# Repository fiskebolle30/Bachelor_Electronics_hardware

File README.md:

# Bachelor_Electronics_hardware
All PCB design files for the bachelor project. Project is made in KiCad

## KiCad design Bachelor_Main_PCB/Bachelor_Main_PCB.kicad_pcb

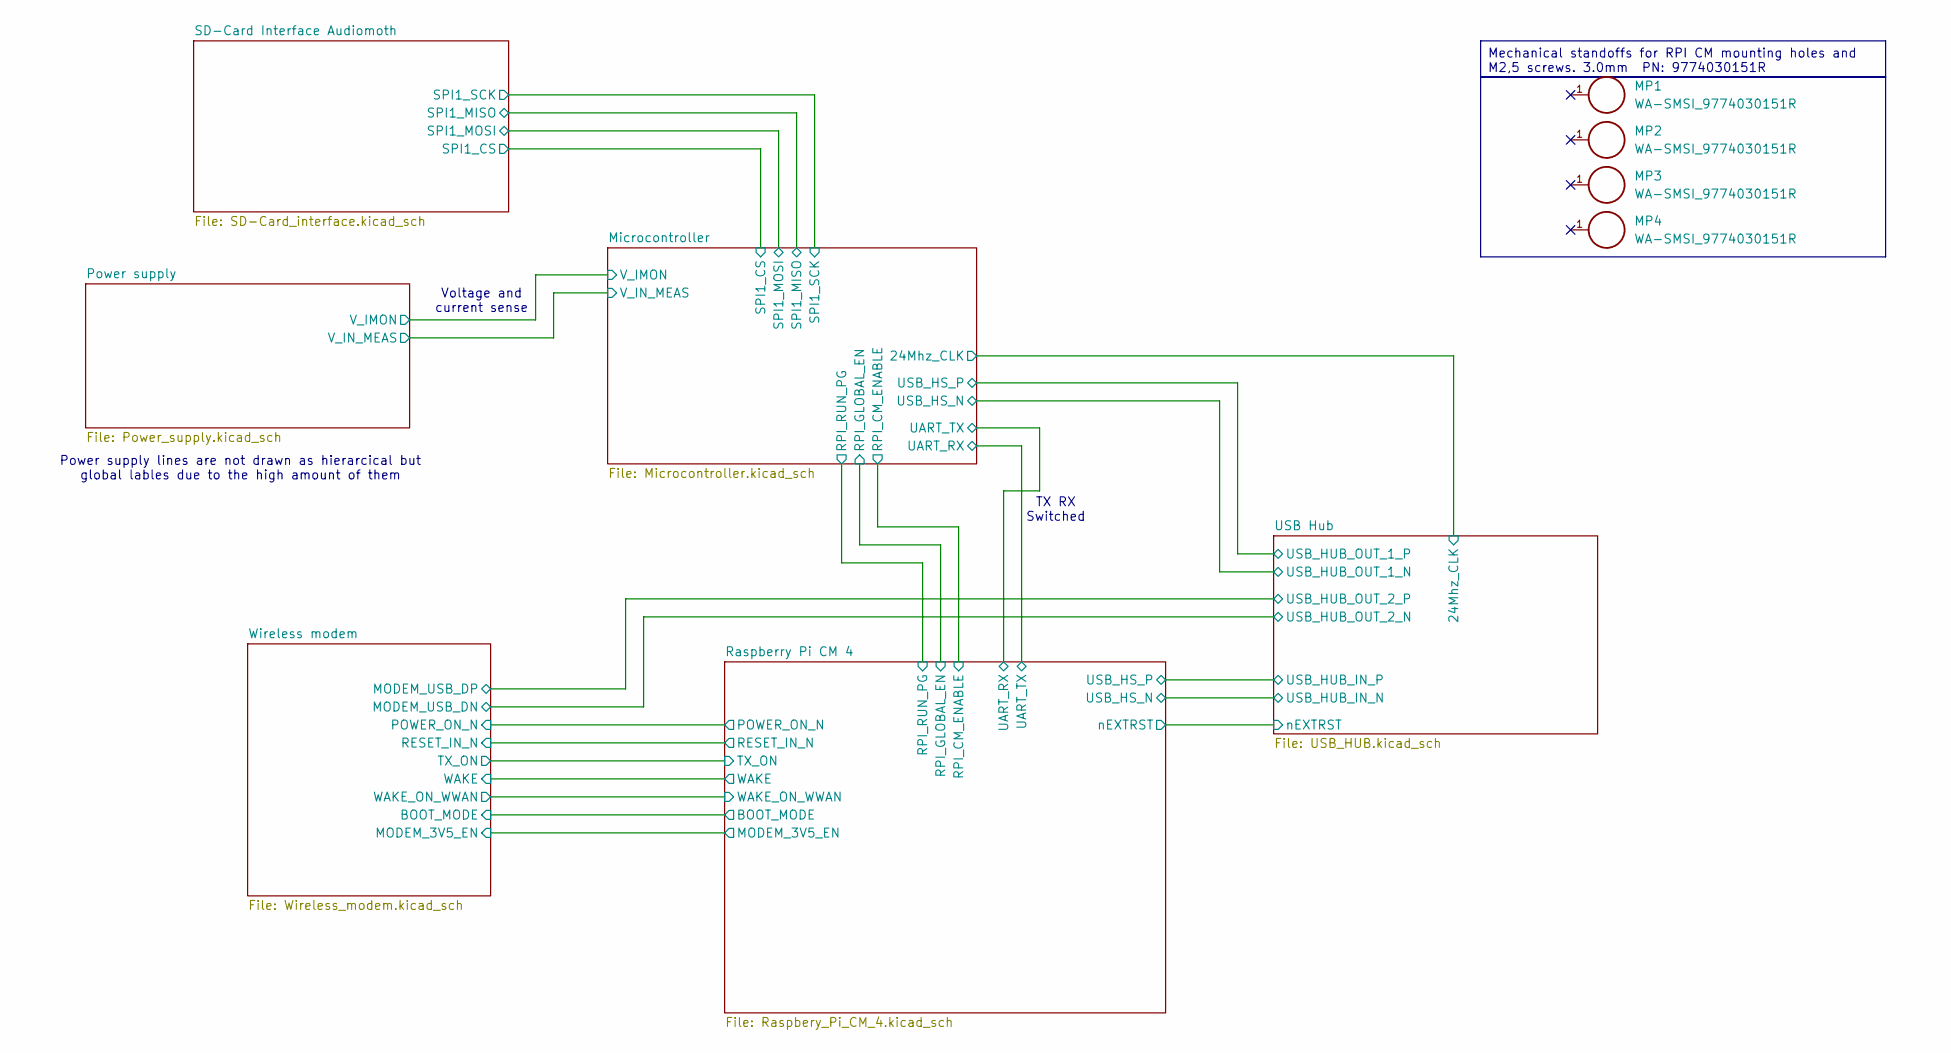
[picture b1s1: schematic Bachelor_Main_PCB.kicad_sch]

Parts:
MP1, MP2, MP3, MP4: WA-SMSI_9774030151R; WA-SMSI_9774030151; PART-NUMBER 9774030151R

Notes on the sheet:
TX RX Switched
Voltage and current sense
Power supply lines are not drawn as hierarcical but global lables due to the high amount of them
Mechanical standoffs for RPI CM mounting holes and M2,5 screws. 3.0mm PN: 9774030151R

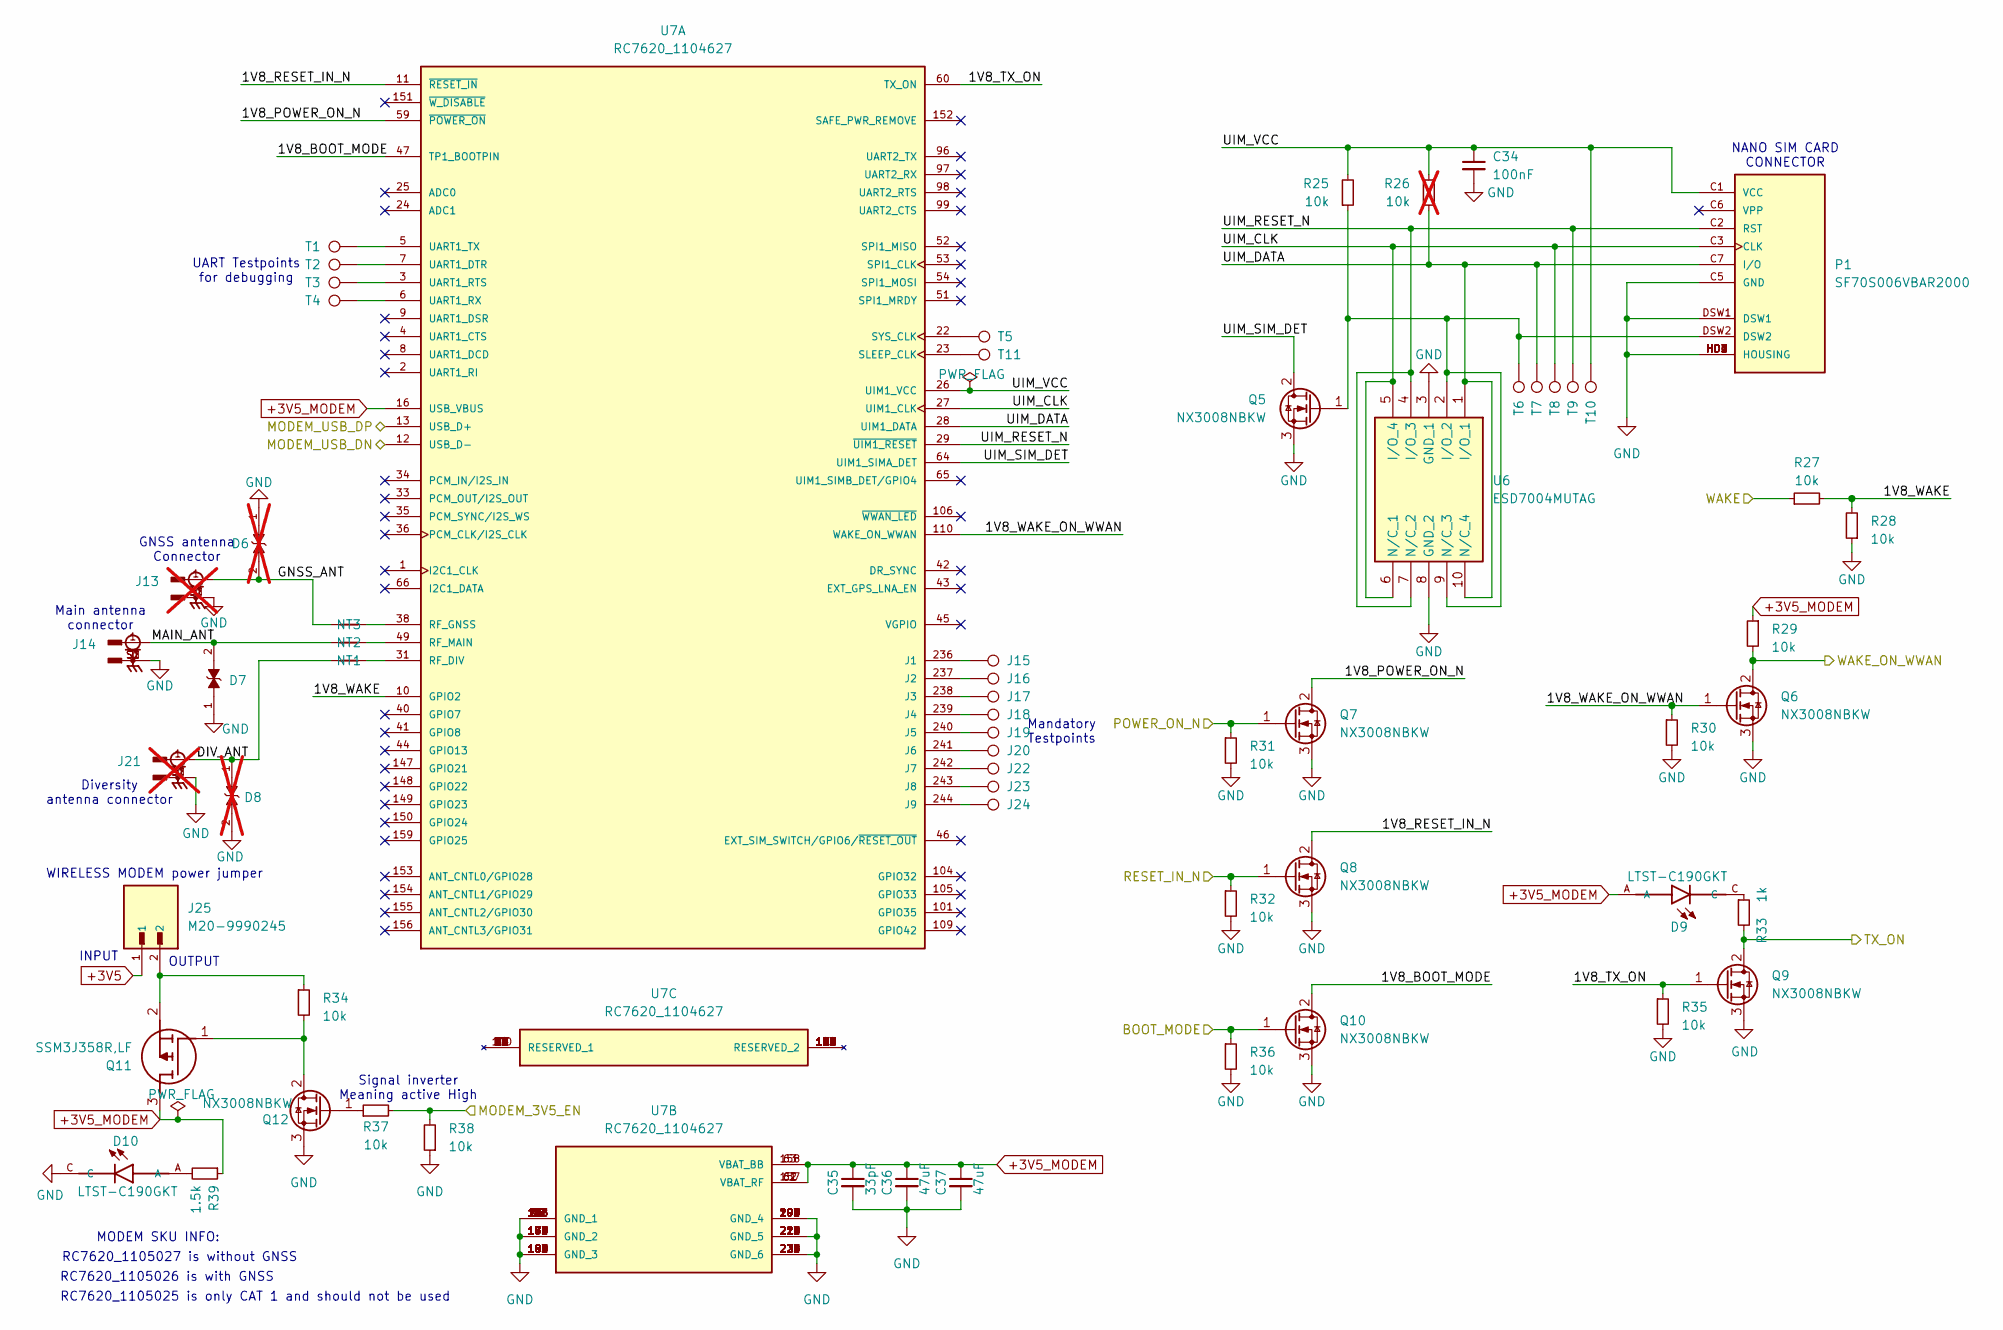
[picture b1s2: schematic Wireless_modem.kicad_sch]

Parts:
C34: 100nF; C_0603_1608Metric; Voltage 50V; Voltage rating 50v; MPN GRM155R71H104KE14D; Mouser 81-GRM155R71H104KE4D
C35: 33pF; C_0603_1608Metric; Voltage rating 50v; Part-no CL10C330JB8NNNC
C36, C37: 47uF; C_1206_3216Metric; Voltage rating 10v; Part-no GRM31CR61A476ME15L
D6, D8: 0402ESDA-MLP1; ESD_0402ESDA-MLP1; Part-no 0402ESDA-MLP1; not fitted
D7: 0402ESDA-MLP1; ESD_0402ESDA-MLP1; Part-no 0402ESDA-MLP1
D9, D10: LTST-C190GKT; LEDM1608X80; Part-no LTST-C190GKT
J13, J21: CONMHF1-SMD-G-T; LINX_CONMHF1-SMD-G-T; Part-no CONMHF1-SMD-G-T; not fitted
J14: CONMHF1-SMD-G-T; LINX_CONMHF1-SMD-G-T; Part-no CONMHF1-SMD-G-T
J15, J16, J17, J18, J19, J20, J22, J23, J24: TestPoint_Pad_D1.0mm
J25: M20-9990245; HARWIN_M20-9990245; PARTREV 14
NT1, NT2, NT3: NetTie_2; 0.3mm_to_0.41_net_tie
P1: SF70S006VBAR2000; JAE_SF70S006VBAR2000
Q5, Q6, Q7, Q8, Q9, Q10, Q12: NX3008NBKW; SOT-323_SC-70; MPN NX3008NBKW; Digikey 1727-1280-6-ND
Q11: SSM3J358R,LF; SOTFL95P240X88-3N; Manufacturer_Part_Number SSM3J358R,LF; Mouser Part Number 757-SSM3J358RLF
R25, R27, R28, R29, R30, R31, R32, R34, R35, R36, R37, R38: 10k; R_0603_1608Metric; Part-no RC0603FR-0710KL
R26: 10k; R_0603_1608Metric; not fitted
R33: 1k; R_0603_1608Metric
R39: 1.5k; R_0603_1608Metric
T1, T2, T3, T4, T5, T6, T7, T8, T9, T10, T11: TestPoint_Pad_D1.0mm
U6: ESD7004MUTAG; UDFN10_CASE_517BB; Manufacturer_Part_Number ESD7004MUTAG; Mouser Part Number 863-ESD7004MUTAG
U7: RC7620_1104627; XCVR_RC7620_1104625; PARTREV 12

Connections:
+3V5: J25.1; also elsewhere on the board
+3V5_MODEM: C35.1, C36.1, C37.1, D9.A, Q11.3 (D), R29.1, R39.1, U7.16 (USB_VBUS), U7.61 (VBAT_RF), U7.62 (VBAT_RF), U7.63 (VBAT_BB), U7.157 (VBAT_RF), U7.158 (VBAT_BB)
/Raspberry Pi CM 4/BOOT_MODE: Q10.1 (G), R36.1; also elsewhere on the board
/Raspberry Pi CM 4/MODEM_3V5_EN: R37.2, R38.2; also elsewhere on the board
/Raspberry Pi CM 4/POWER_ON_N: Q7.1 (G), R31.1; also elsewhere on the board
/Raspberry Pi CM 4/RESET_IN_N: Q8.1 (G), R32.1; also elsewhere on the board
/Raspberry Pi CM 4/TX_ON: Q9.2 (D), R33.2; also elsewhere on the board
/Raspberry Pi CM 4/WAKE: R27.1; also elsewhere on the board
/Raspberry Pi CM 4/WAKE_ON_WWAN: Q6.2 (D), R29.2; also elsewhere on the board
/USB Hub/USB_HUB_OUT_2_N: U7.12 (USB_D-); also elsewhere on the board
/USB Hub/USB_HUB_OUT_2_P: U7.13 (USB_D+); also elsewhere on the board
/Wireless modem/1V8_BOOT_MODE: Q10.2 (D), U7.47 (TP1_BOOTPIN)
/Wireless modem/1V8_POWER_ON_N: Q7.2 (D), U7.59 (~POWER_ON)
/Wireless modem/1V8_RESET_IN_N: Q8.2 (D), U7.11 (~RESET_IN)
/Wireless modem/1V8_TX_ON: Q9.1 (G), R35.1, U7.60 (TX_ON)
/Wireless modem/1V8_WAKE: R27.2, R28.2, U7.10 (GPIO2)
/Wireless modem/1V8_WAKE_ON_WWAN: Q6.1 (G), R30.1, U7.110 (WAKE_ON_WWAN)
/Wireless modem/DIV_ANT: D8.1, J21.1, NT1.1
/Wireless modem/GNSS_ANT: D6.2, J13.1, NT3.1
/Wireless modem/MAIN_ANT: D7.2, J14.1, NT2.1
/Wireless modem/UIM_CLK: P1.C3 (CLK), T8.1, U6.5 (I/O_4), U6.6 (N/C_1), U7.27 (UIM1_CLK)
/Wireless modem/UIM_DATA: P1.C7 (I/O), R26.1, T7.1, U6.1 (I/O_1), U6.10 (N/C_4), U7.28 (UIM1_DATA)
/Wireless modem/UIM_RESET_N: P1.C2 (RST), T9.1, U6.4 (I/O_3), U6.7 (N/C_2), U7.29 (~UIM1_RESET)
/Wireless modem/UIM_SIM_DET: Q5.2 (D), U7.64 (UIM1_SIMA_DET)
/Wireless modem/UIM_VCC: C34.1, P1.C1 (VCC), R25.2, R26.2, T10.1, U7.26 (UIM1_VCC)
GND: C34.2, C35.2, C36.2, C37.2, D6.1, D7.1, D8.2, D10.C, J13.S1, J13.S2, J13.S3, J14.S1, J14.S2, J14.S3, J21.S1, J21.S2, J21.S3, P1.C5 (GND), P1.DSW1, P1.HD1 (HOUSING), P1.HD2 (HOUSING), P1.HD3 (HOUSING), P1.HD4 (HOUSING), P1.HD5 (HOUSING), P1.HD6 (HOUSING), P1.HD7 (HOUSING), Q5.3 (S), Q6.3 (S), Q7.3 (S), Q8.3 (S), Q9.3 (S), Q10.3 (S), Q12.3 (S), R28.1, R30.2, R31.2, R32.2, R35.2, R36.2, R38.1, U6.3 (GND_1), U6.8 (GND_2), U7.30 (GND_1), U7.32 (GND_1), U7.37 (GND_1), U7.39 (GND_1), U7.48 (GND_1), U7.50 (GND_1), U7.67 (GND_1), U7.68 (GND_1), U7.69 (GND_1), U7.70 (GND_1), U7.111 (GND_1), U7.113 (GND_1), U7.125 (GND_1), U7.128 (GND_1), U7.136 (GND_1), U7.139 (GND_2), U7.167 (GND_2), U7.168 (GND_2), U7.169 (GND_2), U7.170 (GND_2), U7.171 (GND_2), U7.172 (GND_2), U7.173 (GND_2), U7.174 (GND_2), U7.175 (GND_2), U7.176 (GND_2), U7.177 (GND_2), U7.178 (GND_2), U7.179 (GND_2), U7.180 (GND_2), U7.181 (GND_3), U7.182 (GND_3), U7.183 (GND_3), U7.184 (GND_3), U7.185 (GND_3), U7.186 (GND_3), U7.187 (GND_3), U7.188 (GND_3), U7.189 (GND_3), U7.190 (GND_3), U7.191 (GND_3), U7.192 (GND_3), U7.193 (GND_3), U7.194 (GND_3), U7.195 (GND_4), U7.196 (GND_4), U7.197 (GND_4), U7.198 (GND_4), U7.199 (GND_4), U7.200 (GND_4), U7.201 (GND_4), U7.202 (GND_4), U7.203 (GND_4), U7.204 (GND_4), U7.205 (GND_4), U7.206 (GND_4), U7.207 (GND_4), U7.208 (GND_4), U7.209 (GND_4), U7.210 (GND_5), U7.211 (GND_5), U7.212 (GND_5), U7.213 (GND_5), U7.214 (GND_5), U7.215 (GND_5), U7.216 (GND_5), U7.217 (GND_5), U7.218 (GND_5), U7.219 (GND_5), U7.220 (GND_5), U7.221 (GND_5), U7.222 (GND_5), U7.223 (GND_5), U7.224 (GND_5), U7.225 (GND_6), U7.226 (GND_6), U7.227 (GND_6), U7.228 (GND_6), U7.229 (GND_6), U7.230 (GND_6), U7.231 (GND_6), U7.232 (GND_6), U7.233 (GND_6), U7.234 (GND_6); also elsewhere on the board
unnamed: D9.C, R33.1
unnamed: D10.A, R39.2
unnamed: P1.DSW2, Q5.1 (G), R25.1, T6.1, U6.2 (I/O_2), U6.9 (N/C_3)
unnamed: Q11.1 (G), Q12.2 (D), R34.2
unnamed: J25.2, Q11.2 (S), R34.1
unnamed: Q12.1 (G), R37.1
unnamed: J15.1, U7.236 (J1)
unnamed: J16.1, U7.237 (J2)
unnamed: J17.1, U7.238 (J3)
unnamed: J18.1, U7.239 (J4)
unnamed: J19.1, U7.240 (J5)
unnamed: J20.1, U7.241 (J6)
unnamed: J22.1, U7.242 (J7)
unnamed: J23.1, U7.243 (J8)
unnamed: J24.1, U7.244 (J9)
unnamed: NT1.2, U7.31 (RF_DIV)
unnamed: NT3.2, U7.38 (RF_GNSS)
unnamed: NT2.2, U7.49 (RF_MAIN)
unnamed: T11.1, U7.23 (SLEEP_CLK)
unnamed: T5.1, U7.22 (SYS_CLK)
unnamed: T2.1, U7.7 (UART1_DTR)
unnamed: T3.1, U7.3 (UART1_RTS)
unnamed: T4.1, U7.6 (UART1_RX)
unnamed: T1.1, U7.5 (UART1_TX)

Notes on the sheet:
Main antenna connector
Diversity antenna connector
NANO SIM CARD CONNECTOR
INPUT
Mandatory Testpoints
OUTPUT
UART Testpoints for debugging
GNSS antenna Connector
RC7620_1105026 is with GNSS
RC7620_1105025 is only CAT 1 and should not be used
MODEM SKU INFO:
Signal inverter Meaning active High
RC7620_1105027 is without GNSS
WIRELESS MODEM power jumper

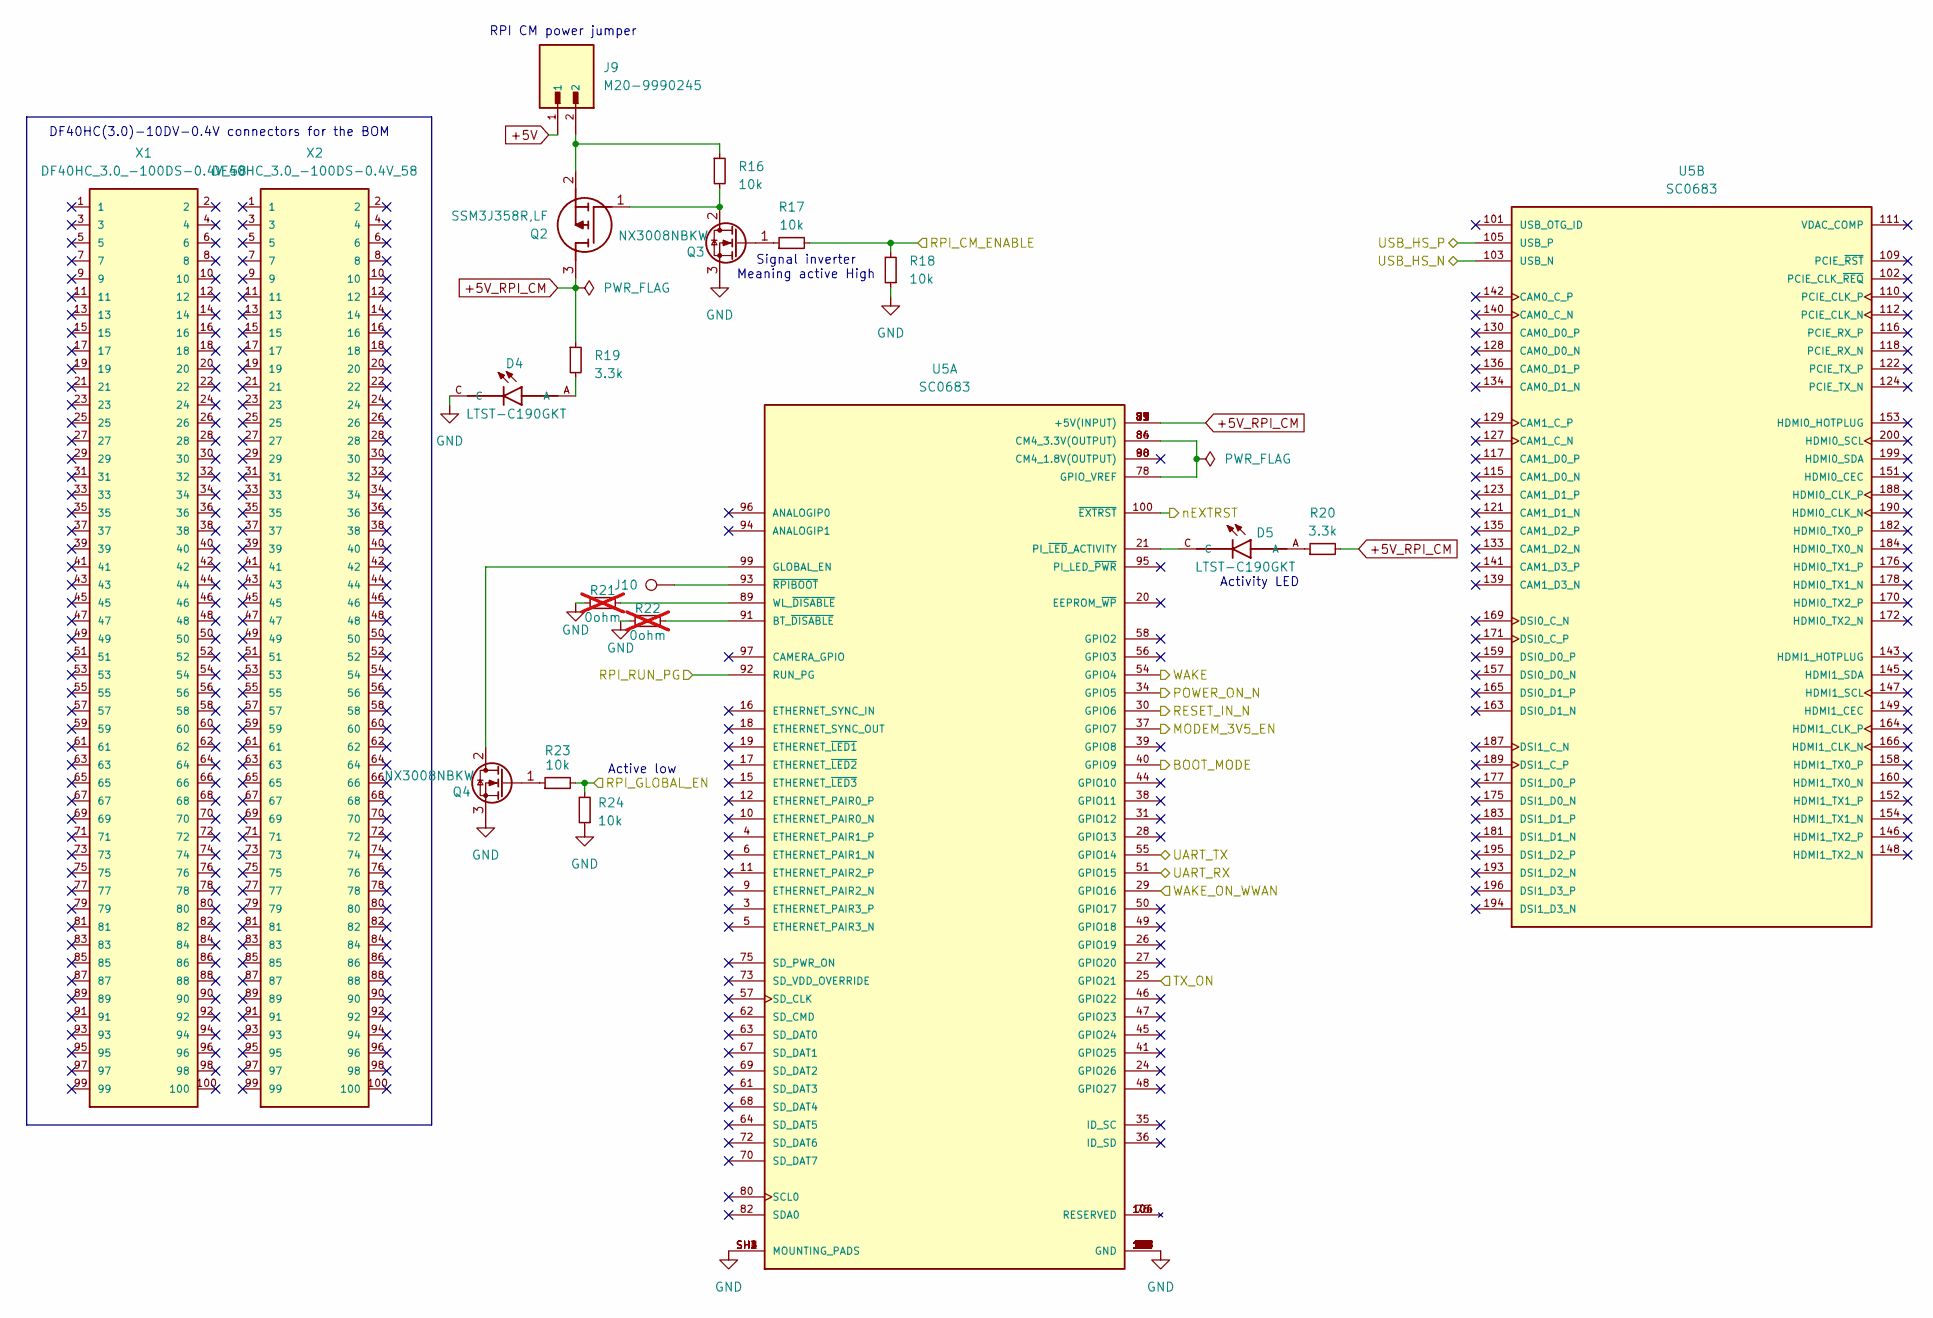
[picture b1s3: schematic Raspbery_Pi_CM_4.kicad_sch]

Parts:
D4, D5: LTST-C190GKT; LEDM1608X80; Part-no LTST-C190GKT
J9: M20-9990245; HARWIN_M20-9990245; PARTREV 14
J10: TestPoint_Pad_D1.0mm
Q2: SSM3J358R,LF; SOTFL95P240X88-3N; Manufacturer_Part_Number SSM3J358R,LF; Mouser Part Number 757-SSM3J358RLF
Q3, Q4: NX3008NBKW; SOT-323_SC-70; MPN NX3008NBKW; Digikey 1727-1280-6-ND
R16, R17, R18, R23, R24: 10k; R_0603_1608Metric; Part-no RC0603FR-0710KL
R19, R20: 3.3k; R_0603_1608Metric
R21, R22: 0ohm; R_0603_1608Metric; not fitted
U5: SC0683; MODULE_SC0683; PARTREV 2021-10-12
X1, X2: DF40HC_3.0_-100DS-0.4V_58; HRS_DF40HC_3.0_-100DS-0.4V_58; Part-no DF40HC_3.0_-100DS-0.4V_58

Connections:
+5V: J9.1; also elsewhere on the board
+5V_RPI_CM: Q2.3 (D), R19.1, R20.2, U5.77 (+5V(INPUT)), U5.79 (+5V(INPUT)), U5.81 (+5V(INPUT)), U5.83 (+5V(INPUT)), U5.85 (+5V(INPUT)), U5.87 (+5V(INPUT))
/Microcontroller/RPI_CM_ENABLE: R17.2, R18.2; also elsewhere on the board
/Microcontroller/RPI_GLOBAL_EN: R23.2, R24.2; also elsewhere on the board
/Microcontroller/RPI_RUN_PG: U5.92 (RUN_PG); also elsewhere on the board
/Microcontroller/UART_RX: U5.55 (GPIO14); also elsewhere on the board
/Microcontroller/UART_TX: U5.51 (GPIO15); also elsewhere on the board
/Raspberry Pi CM 4/BOOT_MODE: U5.40 (GPIO9); also elsewhere on the board
/Raspberry Pi CM 4/MODEM_3V5_EN: U5.37 (GPIO7); also elsewhere on the board
/Raspberry Pi CM 4/POWER_ON_N: U5.34 (GPIO5); also elsewhere on the board
/Raspberry Pi CM 4/RESET_IN_N: U5.30 (GPIO6); also elsewhere on the board
/Raspberry Pi CM 4/TX_ON: U5.25 (GPIO21); also elsewhere on the board
/Raspberry Pi CM 4/USB_HS_N: U5.103 (USB_N); also elsewhere on the board
/Raspberry Pi CM 4/USB_HS_P: U5.105 (USB_P); also elsewhere on the board
/Raspberry Pi CM 4/WAKE: U5.54 (GPIO4); also elsewhere on the board
/Raspberry Pi CM 4/WAKE_ON_WWAN: U5.29 (GPIO16); also elsewhere on the board
/Raspberry Pi CM 4/nEXTRST: U5.100 (~EXTRST); also elsewhere on the board
GND: D4.C, Q3.3 (S), Q4.3 (S), R18.1, R21.1, R22.1, R24.1, U5.1 (GND), U5.2 (GND), U5.7 (GND), U5.8 (GND), U5.13 (GND), U5.14 (GND), U5.22 (GND), U5.23 (GND), U5.32 (GND), U5.33 (GND), U5.42 (GND), U5.43 (GND), U5.52 (GND), U5.53 (GND), U5.59 (GND), U5.60 (GND), U5.65 (GND), U5.66 (GND), U5.71 (GND), U5.74 (GND), U5.98 (GND), U5.107 (GND), U5.108 (GND), U5.113 (GND), U5.114 (GND), U5.119 (GND), U5.120 (GND), U5.125 (GND), U5.126 (GND), U5.131 (GND), U5.132 (GND), U5.137 (GND), U5.138 (GND), U5.144 (GND), U5.150 (GND), U5.155 (GND), U5.156 (GND), U5.161 (GND), U5.162 (GND), U5.167 (GND), U5.168 (GND), U5.173 (GND), U5.174 (GND), U5.179 (GND), U5.180 (GND), U5.185 (GND), U5.186 (GND), U5.191 (GND), U5.192 (GND), U5.197 (GND), U5.198 (GND), U5.SH1 (MOUNTING_PADS), U5.SH2 (MOUNTING_PADS), U5.SH3 (MOUNTING_PADS), U5.SH4 (MOUNTING_PADS); also elsewhere on the board
unnamed: D4.A, R19.2
unnamed: D5.A, R20.1
unnamed: Q2.1 (G), Q3.2 (D), R16.2
unnamed: J9.2, Q2.2 (S), R16.1
unnamed: Q3.1 (G), R17.1
unnamed: Q4.2 (D), U5.99 (GLOBAL_EN)
unnamed: Q4.1 (G), R23.1
unnamed: R22.2, U5.91 (BT_~DISABLE)
unnamed: U5.78 (GPIO_VREF), U5.84 (CM4_3.3V(OUTPUT)), U5.86 (CM4_3.3V(OUTPUT))
unnamed: D5.C, U5.21 (PI_~LED_ACTIVITY)
unnamed: R21.2, U5.89 (WL_~DISABLE)
unnamed: J10.1, U5.93 (~RPIBOOT)

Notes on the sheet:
Signal inverter Meaning active High
Active low
RPI CM power jumper
DF40HC(3.0)-10DV-0.4V connectors for the BOM
Activity LED

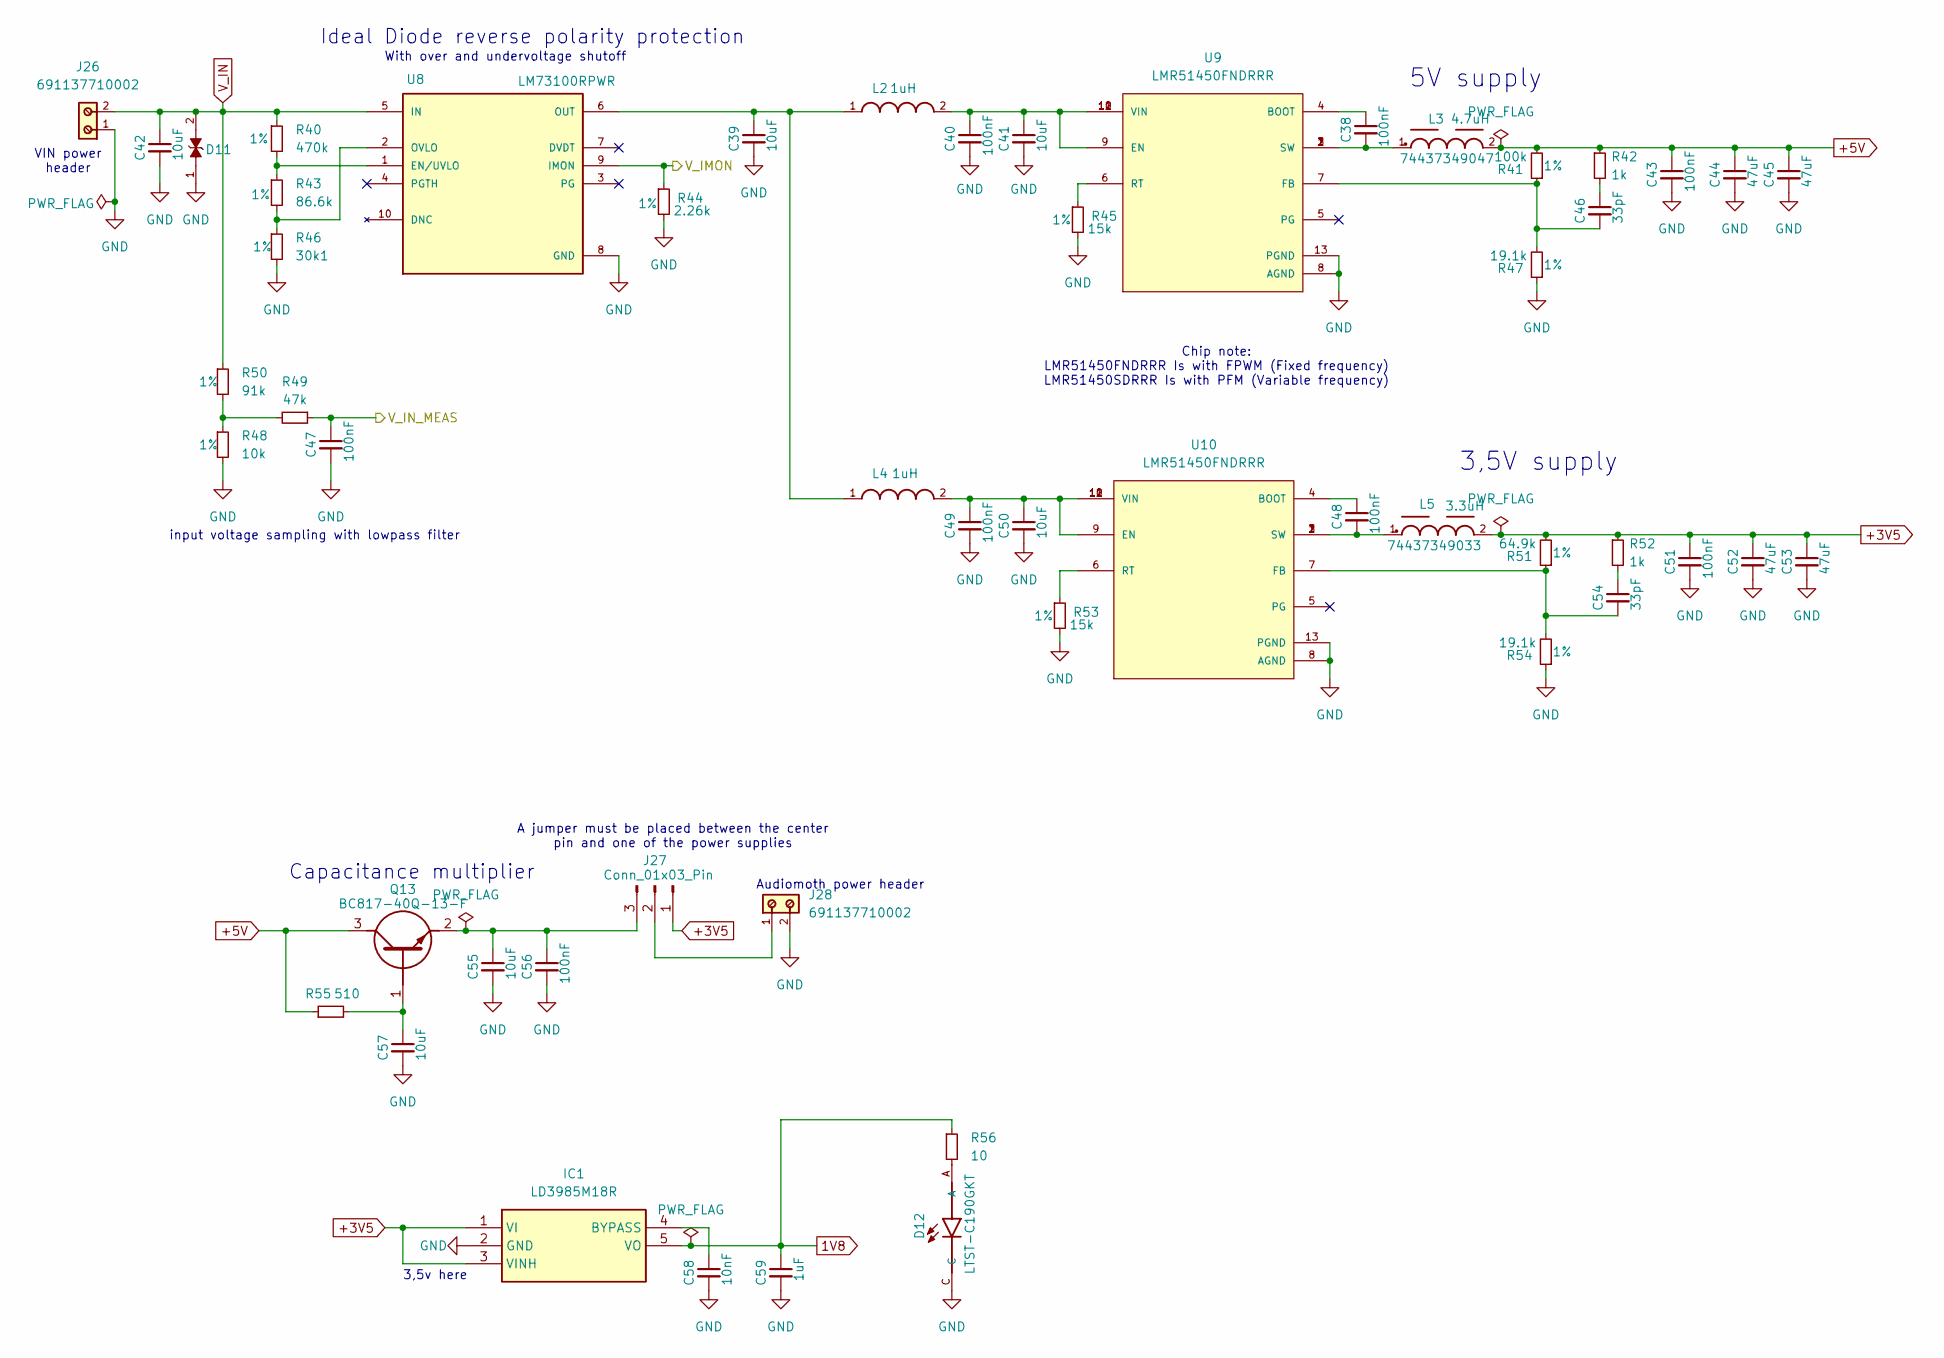
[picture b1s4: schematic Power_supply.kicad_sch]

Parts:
C38, C40, C43, C47, C48, C49, C51, C56: 100nF; C_0603_1608Metric; Voltage rating 50v; Part-no CL10B104KB8NNWC
C39, C41, C42, C50, C55, C57: 10uF; C_1206_3216Metric; Voltage rating 50v; Part-no CL31B106KBHNNNE
C44, C45, C52, C53: 47uF; C_1206_3216Metric; Voltage rating 10v; Part-no GRM31CR61A476ME15L
C46, C54: 33pF; C_0603_1608Metric; Voltage rating 50v; Part-no CL10C330JB8NNNC
C58: 10nF; C_0603_1608Metric; Voltage rating 50v; Part-no CL10B103KB8NNNC
C59: 1uF; C_0603_1608Metric; Voltage rating 16v; Part-no CL10B105KO8NNNC
D11: 0402ESDA-MLP1; ESD_0402ESDA-MLP1; Part-no 0402ESDA-MLP1
D12: LTST-C190GKT; LEDM1608X80; Part-no LTST-C190GKT
IC1: LD3985M18R; SOT95P280X145-5N; Manufacturer_Part_Number LD3985M18R; Mouser Part Number 511-LD3985M18R
J26, J28: 691137710002; Part-no 691137710002
J27: Conn_01x03_Pin; PinHeader_1x03_P2.54mm_Vertical
L2, L4: 1uH; INDC2520X120N; Part-no LQM2HPN1R0MJHL
L3: 4.7uH; WE-LHMI_7050; Part-no 74437349047
L5: 3.3uH; WE-LHMI_7050; Part-no 74437349033
Q13: BC817-40Q-13-F; SOT96P240X110-3N; Manufacturer_Part_Number BC817-40Q-13-F; Mouser Part Number 621-BC817-40Q-13-F
R40: 470k; R_0603_1608Metric; Tolerance 1%; Part-no RMCF0603FT470K
R41: 100k; R_0603_1608Metric; Tolerance 1%; Part-no RMCF0603FT100K
R42, R52: 1k; R_0603_1608Metric
R43: 86.6k; R_0603_1608Metric; Tolerance 1%; Part-no RC0603FR-0786K6L
R44: 2.26k; R_0603_1608Metric; Tolerance 1%; Part-no RC0603FR-072K26L
R45, R53: 15k; R_0603_1608Metric; Tolerance 1%; Part-no RC0603FR-0715KL
R46: 30k1; R_0603_1608Metric; Tolerance 1%; Part-no RMCF0603FT30K1
R47, R54: 19.1k; R_0603_1608Metric; Tolerance 1%; Part-no RC0603FR-0719K1L
R48: 10k; R_0603_1608Metric; Tolerance 1%; Part-no RC0603FR-0710KL
R49: 47k; R_0603_1608Metric
R50: 91k; R_0603_1608Metric; Tolerance 1%; Part-no RC0603FR-0791KL
R51: 64.9k; R_0603_1608Metric; Tolerance 1%; Part-no RC0603FR-0764K9L
R55: 510; R_0603_1608Metric
R56: 10; R_0603_1608Metric
U8: LM73100RPWR; IC_LM73100RPWR; PARTREV 08/2019
U9, U10: LMR51450FNDRRR; CONV_LMR51450FNDRRR; PARTREV December 2022

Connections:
1V8: C59.1, IC1.5 (VO), R56.1; also elsewhere on the board
+3V5: C51.1, C52.1, C53.1, IC1.1 (VI), IC1.3 (VINH), J27.1, L5.2, R51.2, R52.1; also elsewhere on the board
+5V: C43.1, C44.1, C45.1, L3.2, Q13.3 (C), R41.2, R42.1, R55.1; also elsewhere on the board
/Microcontroller/V_IMON: R44.1, U8.9 (IMON); also elsewhere on the board
/Microcontroller/V_IN_MEAS: C47.1, R49.1; also elsewhere on the board
GND: C39.2, C40.2, C41.2, C42.2, C43.2, C44.2, C45.2, C47.2, C49.2, C50.2, C51.2, C52.2, C53.2, C55.2, C56.2, C57.2, C58.2, C59.2, D11.1, D12.C, IC1.2 (GND), J26.1, J28.2, R44.2, R45.2, R46.2, R47.1, R48.2, R53.2, R54.1, U8.8 (GND), U9.8 (AGND), U9.13 (PGND), U10.8 (AGND), U10.13 (PGND); also elsewhere on the board
unnamed: C38.2, L3.1, U9.1 (SW), U9.2 (SW), U9.3 (SW)
unnamed: C46.1, R42.2
unnamed: C48.2, L5.1, U10.1 (SW), U10.2 (SW), U10.3 (SW)
unnamed: C54.1, R52.2
unnamed: D12.A, R56.2
unnamed: C58.1, IC1.4 (BYPASS)
unnamed: J27.2, J28.1
unnamed: C55.1, C56.1, J27.3, Q13.2 (E)
unnamed: C57.1, Q13.1 (B), R55.2
unnamed: R48.1, R49.2, R50.2
unnamed: R40.2, R43.1, U8.1 (EN/UVLO)
unnamed: C39.1, L2.1, L4.1, U8.6 (OUT)
unnamed: R43.2, R46.1, U8.2 (OVLO)
unnamed: C38.1, U9.4 (BOOT)
unnamed: C40.1, C41.1, L2.2, U9.9 (EN), U9.10 (VIN), U9.11 (VIN), U9.12 (VIN)
unnamed: C46.2, R41.1, R47.2, U9.7 (FB)
unnamed: R45.1, U9.6 (RT)
unnamed: C48.1, U10.4 (BOOT)
unnamed: C49.1, C50.1, L4.2, U10.9 (EN), U10.10 (VIN), U10.11 (VIN), U10.12 (VIN)
unnamed: C54.2, R51.1, R54.2, U10.7 (FB)
unnamed: R53.1, U10.6 (RT)
V_IN: C42.1, D11.2, J26.2, R40.1, R50.1, U8.5 (IN)

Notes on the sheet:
5V supply
Ideal Diode reverse polarity protection
Chip note: LMR51450FNDRRR Is with FPWM (Fixed frequency) LMR51450SDRRR Is with PFM (Variable frequency)
input voltage sampling with lowpass filter
3,5v here
Audiomoth power header
With over and undervoltage shutoff
Capacitance multiplier
3,5V supply
VIN power header
A jumper must be placed between the center pin and one of the power supplies
